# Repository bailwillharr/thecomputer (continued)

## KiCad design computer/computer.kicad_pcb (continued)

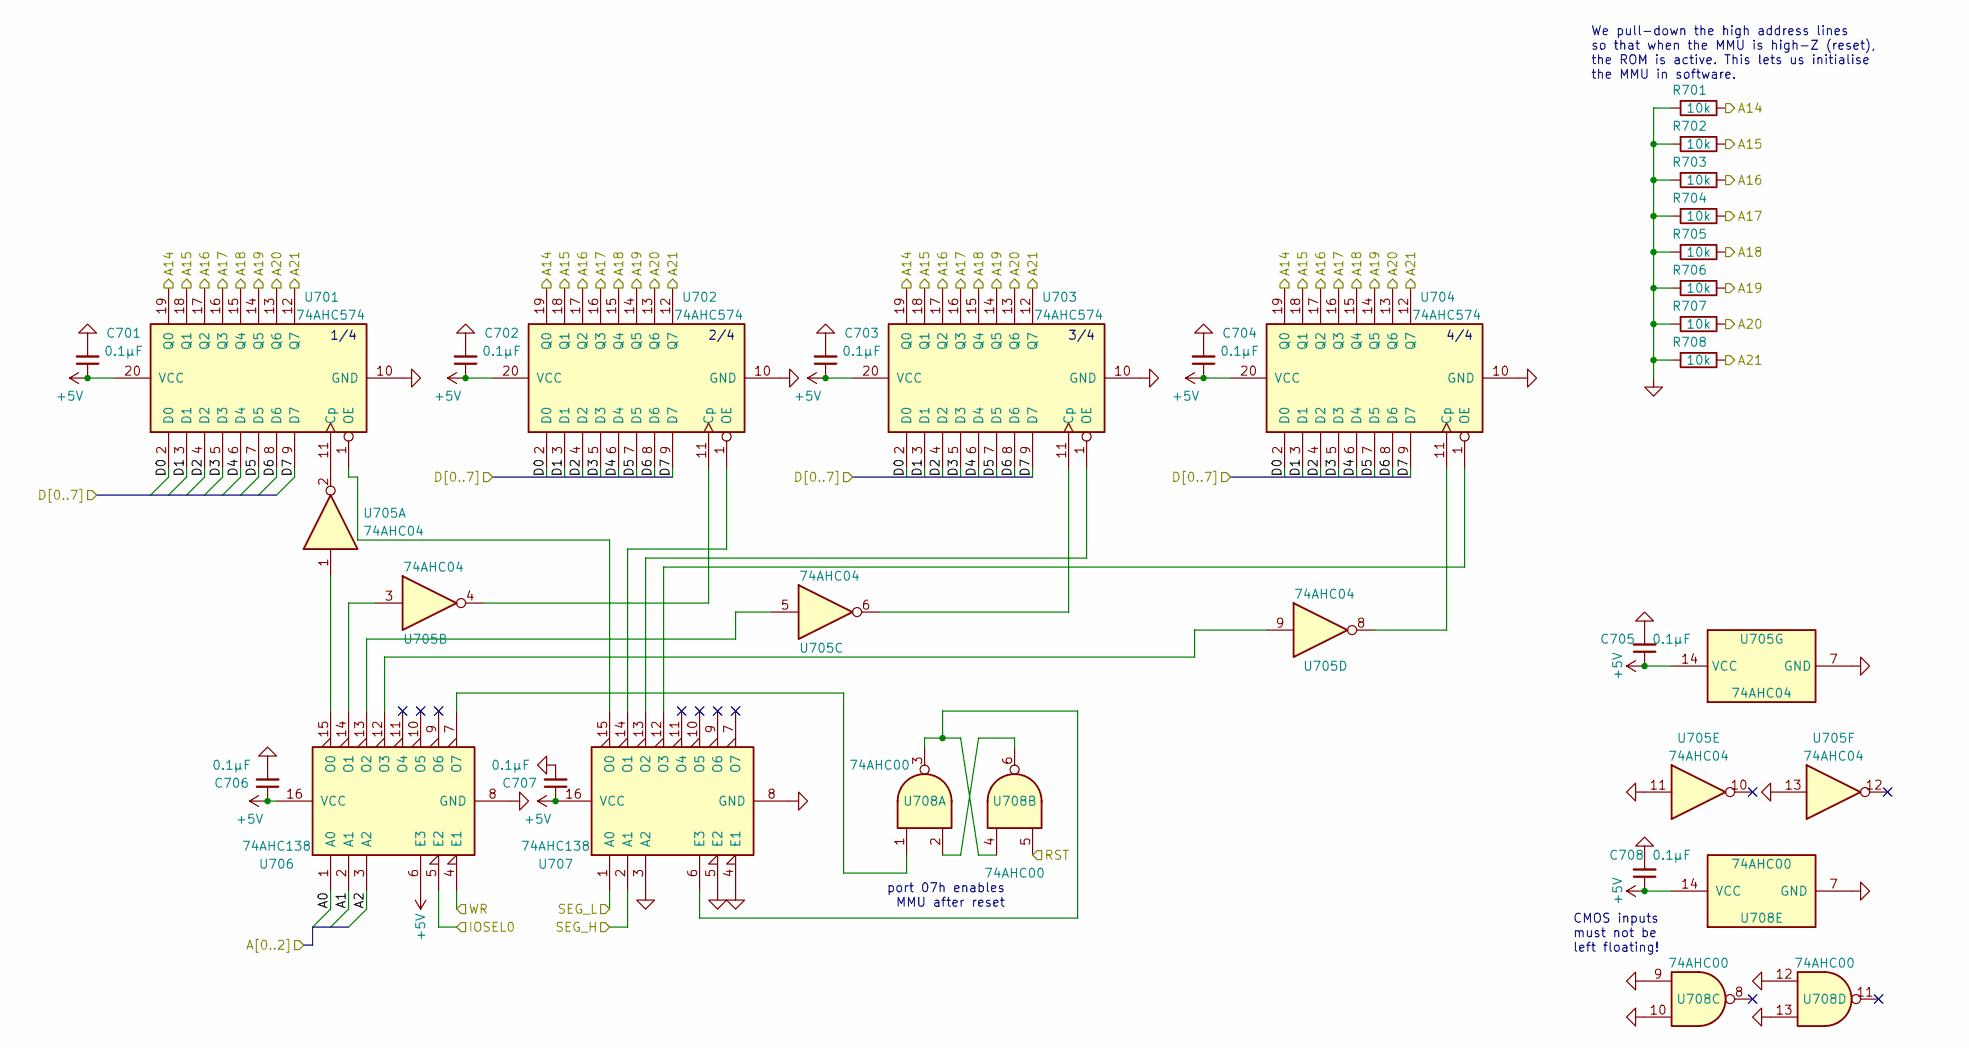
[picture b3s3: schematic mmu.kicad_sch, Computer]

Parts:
C701, C702, C703, C704, C705, C706, C707, C708: 0.1µF; C_Disc_D5.0mm_W2.5mm_P2.50mm
R701, R702, R703, R704, R705, R706, R707, R708: 10k; R_Axial_DIN0207_L6.3mm_D2.5mm_P10.16mm_Horizontal
U701, U702, U703, U704: 74AHC574; DIP-20_W7.62mm_Socket_LongPads
U705: 74AHC04; DIP-14_W7.62mm_Socket_LongPads
U706, U707: 74AHC138; DIP-16_W7.62mm_Socket_LongPads
U708: 74AHC00; DIP-14_W7.62mm_Socket_LongPads

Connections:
+5V: C701.1, C702.1, C703.1, C704.1, C705.1, C706.1, C707.1, C708.1, U701.20 (VCC), U702.20 (VCC), U703.20 (VCC), U704.20 (VCC), U705.14 (VCC), U706.6 (E3), U706.16 (VCC), U707.16 (VCC), U708.14 (VCC); also elsewhere on the board
A0: U706.1 (A0); also elsewhere on the board
A1: U706.2 (A1); also elsewhere on the board
A2: U706.3 (A2); also elsewhere on the board
A14: R701.1, U701.19 (Q0), U702.19 (Q0), U703.19 (Q0), U704.19 (Q0); also elsewhere on the board
A15: R702.1, U701.18 (Q1), U702.18 (Q1), U703.18 (Q1), U704.18 (Q1); also elsewhere on the board
A16: R703.1, U701.17 (Q2), U702.17 (Q2), U703.17 (Q2), U704.17 (Q2); also elsewhere on the board
A17: R704.1, U701.16 (Q3), U702.16 (Q3), U703.16 (Q3), U704.16 (Q3); also elsewhere on the board
A18: R705.1, U701.15 (Q4), U702.15 (Q4), U703.15 (Q4), U704.15 (Q4); also elsewhere on the board
A19: R706.1, U701.14 (Q5), U702.14 (Q5), U703.14 (Q5), U704.14 (Q5); also elsewhere on the board
A20: R707.1, U701.13 (Q6), U702.13 (Q6), U703.13 (Q6), U704.13 (Q6); also elsewhere on the board
A21: R708.1, U701.12 (Q7), U702.12 (Q7), U703.12 (Q7), U704.12 (Q7); also elsewhere on the board
CPU_A14: U707.1 (A0); also elsewhere on the board
CPU_A15: U707.2 (A1); also elsewhere on the board
D0: U701.2 (D0), U702.2 (D0), U703.2 (D0), U704.2 (D0); also elsewhere on the board
D1: U701.3 (D1), U702.3 (D1), U703.3 (D1), U704.3 (D1); also elsewhere on the board
D2: U701.4 (D2), U702.4 (D2), U703.4 (D2), U704.4 (D2); also elsewhere on the board
D3: U701.5 (D3), U702.5 (D3), U703.5 (D3), U704.5 (D3); also elsewhere on the board
D4: U701.6 (D4), U702.6 (D4), U703.6 (D4), U704.6 (D4); also elsewhere on the board
D5: U701.7 (D5), U702.7 (D5), U703.7 (D5), U704.7 (D5); also elsewhere on the board
D6: U701.8 (D6), U702.8 (D6), U703.8 (D6), U704.8 (D6); also elsewhere on the board
D7: U701.9 (D7), U702.9 (D7), U703.9 (D7), U704.9 (D7); also elsewhere on the board
GND: C701.2, C702.2, C703.2, C704.2, C705.2, C706.2, C707.2, C708.2, R701.2, R702.2, R703.2, R704.2, R705.2, R706.2, R707.2, R708.2, U701.10 (GND), U702.10 (GND), U703.10 (GND), U704.10 (GND), U705.7 (GND), U705.11, U705.13, U706.8 (GND), U707.3 (A2), U707.4 (E1), U707.5 (E2), U707.8 (GND), U708.7 (GND), U708.9, U708.10, U708.12, U708.13; also elsewhere on the board
IOSEL0: U706.5 (E2); also elsewhere on the board
unnamed: U701.1 (OE), U707.15 (O0)
unnamed: U701.11 (Cp), U705.2
unnamed: U702.1 (OE), U707.14 (O1)
unnamed: U702.11 (Cp), U705.4
unnamed: U703.1 (OE), U707.13 (O2)
unnamed: U703.11 (Cp), U705.6
unnamed: U704.1 (OE), U707.12 (O3)
unnamed: U704.11 (Cp), U705.8
unnamed: U705.1, U706.15 (O0)
unnamed: U705.3, U706.14 (O1)
unnamed: U705.5, U706.13 (O2)
unnamed: U705.9, U706.12 (O3)
unnamed: U706.7 (O7), U708.1
unnamed: U707.6 (E3), U708.3, U708.4
unnamed: U708.2, U708.6
RST: U708.5; also elsewhere on the board
WR: U706.4 (E1); also elsewhere on the board

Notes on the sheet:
1/4
4/4
2/4
We pull-down the high address lines so that when the MMU is high-Z (reset), the ROM is active. This lets us initialise the MMU in software.
port 07h enables MMU after reset
CMOS inputs must not be left floating!
3/4

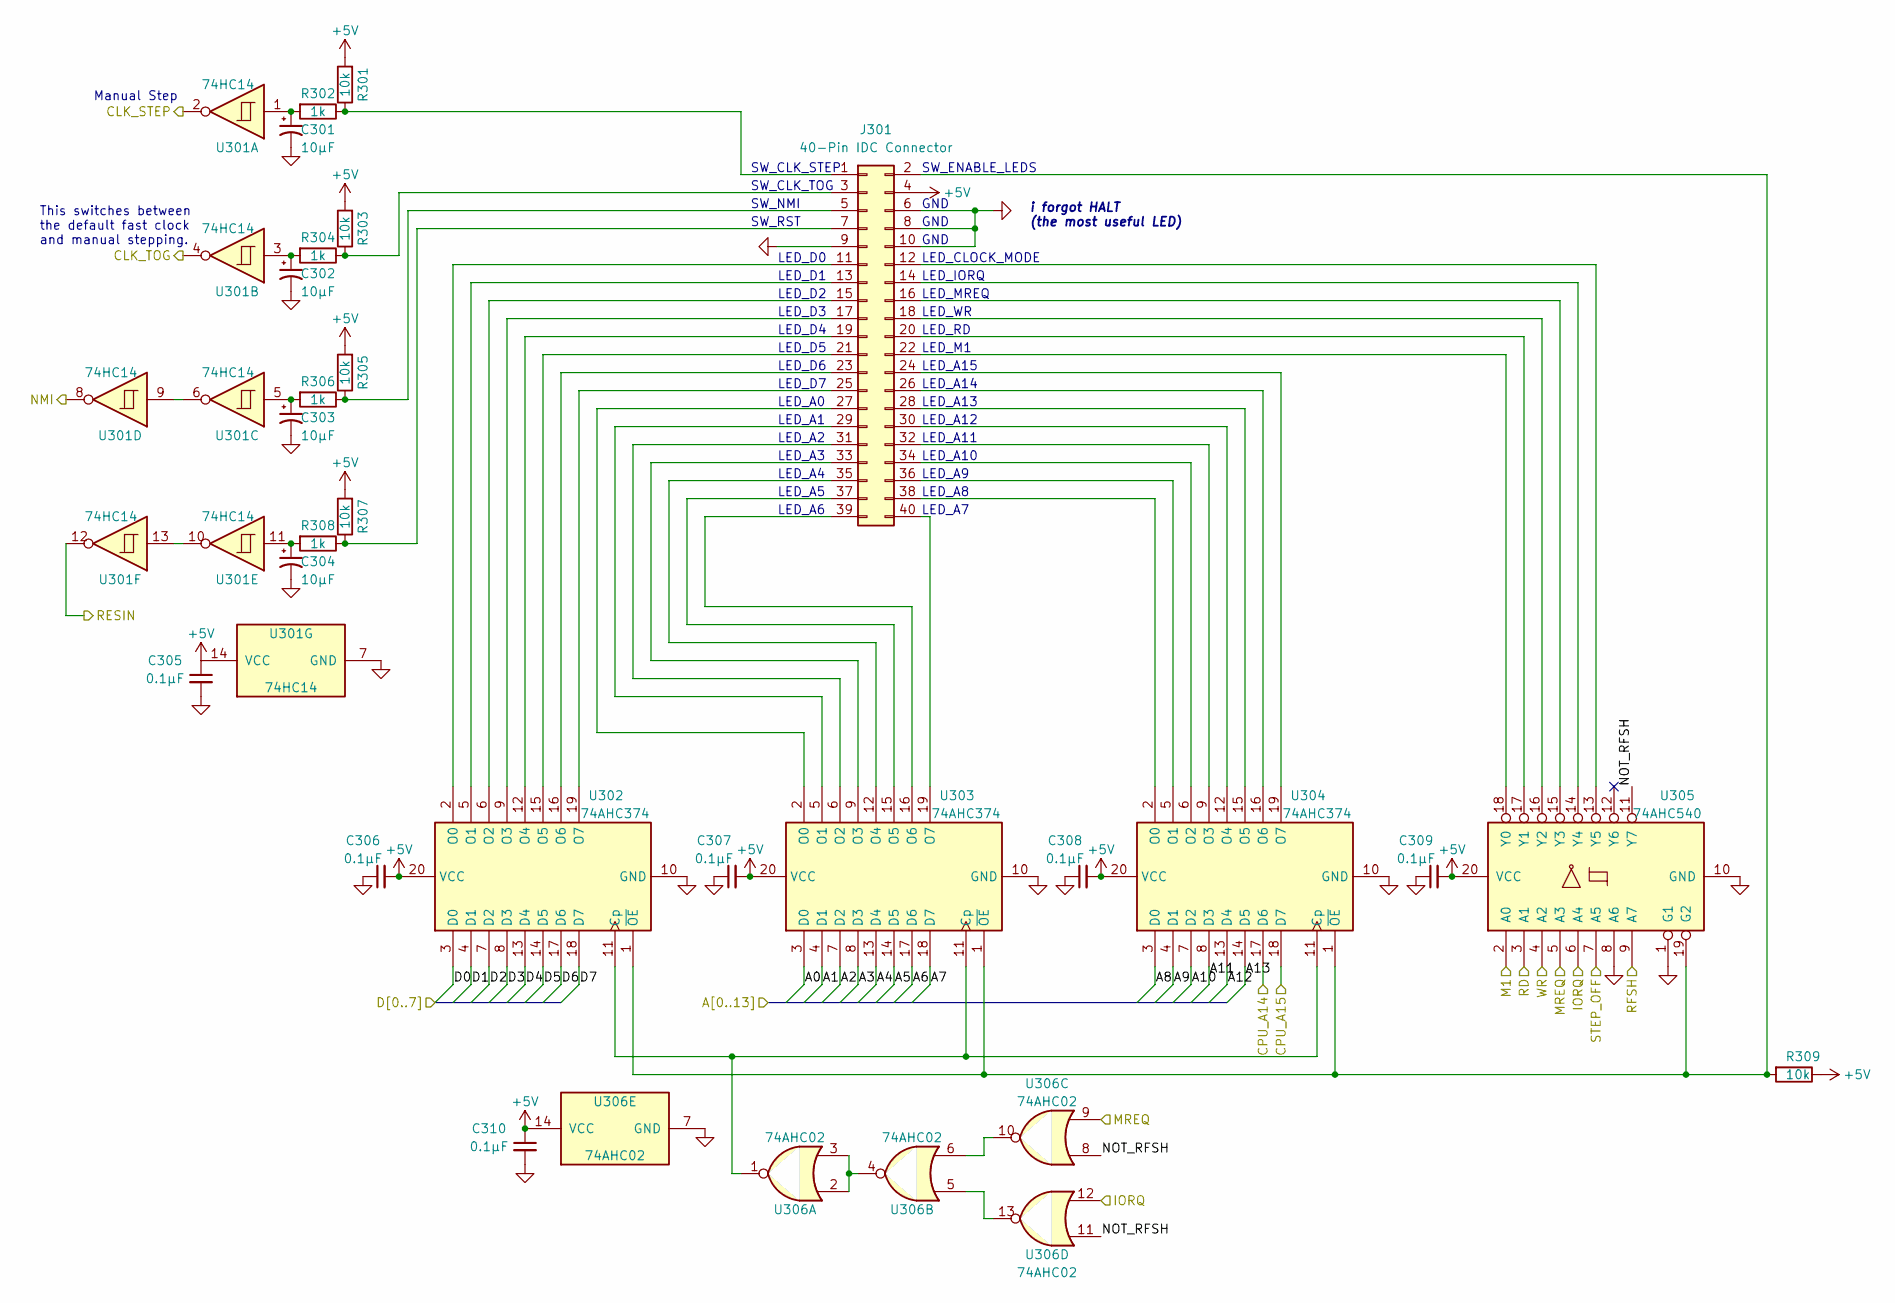
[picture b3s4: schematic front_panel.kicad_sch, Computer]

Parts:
C301, C302, C303, C304: 10µF; CP_Radial_D5.0mm_P2.50mm
C305, C306, C307, C308, C309, C310: 0.1µF; C_Disc_D5.0mm_W2.5mm_P2.50mm
J301: 40-Pin IDC Connector; IDC-Header_2x20_P2.54mm_Vertical
R301, R303, R305, R307, R309: 10k; R_Axial_DIN0207_L6.3mm_D2.5mm_P10.16mm_Horizontal
R302, R304, R306, R308: 1k; R_Axial_DIN0207_L6.3mm_D2.5mm_P10.16mm_Horizontal
U301: 74HC14; DIP-14_W7.62mm_Socket_LongPads
U302, U303, U304: 74AHC374; DIP-20_W7.62mm_Socket_LongPads
U305: 74AHC540; DIP-20_W7.62mm_Socket_LongPads
U306: 74AHC02; DIP-14_W7.62mm_Socket_LongPads

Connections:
+5V: C305.1, C306.2, C307.2, C308.2, C309.2, C310.1, J301.4, R301.2, R303.2, R305.2, R307.2, R309.1, U301.14 (VCC), U302.20 (VCC), U303.20 (VCC), U304.20 (VCC), U305.20 (VCC), U306.14 (VCC); also elsewhere on the board
/CLOCK/CLK_MAN: U301.2; also elsewhere on the board
/CLOCK/CLK_TOG: U301.4; also elsewhere on the board
/CLOCK/STEP_OFF: U305.7 (A5); also elsewhere on the board
/FRONT_PANEL/NOT_RFSH: U305.11 (Y7), U306.8, U306.11
A0: U303.3 (D0); also elsewhere on the board
A1: U303.4 (D1); also elsewhere on the board
A2: U303.7 (D2); also elsewhere on the board
A3: U303.8 (D3); also elsewhere on the board
A4: U303.13 (D4); also elsewhere on the board
A5: U303.14 (D5); also elsewhere on the board
A6: U303.17 (D6); also elsewhere on the board
A7: U303.18 (D7); also elsewhere on the board
A8: U304.3 (D0); also elsewhere on the board
A9: U304.4 (D1); also elsewhere on the board
A10: U304.7 (D2); also elsewhere on the board
A11: U304.8 (D3); also elsewhere on the board
A12: U304.13 (D4); also elsewhere on the board
A13: U304.14 (D5); also elsewhere on the board
CPU_A14: U304.17 (D6); also elsewhere on the board
CPU_A15: U304.18 (D7); also elsewhere on the board
D0: U302.3 (D0); also elsewhere on the board
D1: U302.4 (D1); also elsewhere on the board
D2: U302.7 (D2); also elsewhere on the board
D3: U302.8 (D3); also elsewhere on the board
D4: U302.13 (D4); also elsewhere on the board
D5: U302.14 (D5); also elsewhere on the board
D6: U302.17 (D6); also elsewhere on the board
D7: U302.18 (D7); also elsewhere on the board
GND: C301.2, C302.2, C303.2, C304.2, C305.2, C306.1, C307.1, C308.1, C309.1, C310.2, J301.6, J301.8, J301.9, J301.10, U301.7 (GND), U302.10 (GND), U303.10 (GND), U304.10 (GND), U305.1 (G1), U305.8 (A6), U305.10 (GND), U306.7 (GND); also elsewhere on the board
IORQ: U305.6 (A4), U306.12; also elsewhere on the board
M1: U305.2 (A0); also elsewhere on the board
MREQ: U305.5 (A3), U306.9; also elsewhere on the board
NMI: U301.8; also elsewhere on the board
unnamed: C301.1, R302.2, U301.1
unnamed: C302.1, R304.2, U301.3
unnamed: C303.1, R306.2, U301.5
unnamed: C304.1, R308.2, U301.11
unnamed: J301.1, R301.1, R302.1
unnamed: J301.2, R309.2, U302.1 (~OE), U303.1 (~OE), U304.1 (~OE), U305.19 (G2)
unnamed: J301.3, R303.1, R304.1
unnamed: J301.5, R305.1, R306.1
unnamed: J301.7, R307.1, R308.1
unnamed: J301.11, U302.2 (O0)
unnamed: J301.12, U305.13 (Y5)
unnamed: J301.13, U302.5 (O1)
unnamed: J301.14, U305.14 (Y4)
unnamed: J301.15, U302.6 (O2)
unnamed: J301.16, U305.15 (Y3)
unnamed: J301.17, U302.9 (O3)
unnamed: J301.18, U305.16 (Y2)
unnamed: J301.19, U302.12 (O4)
unnamed: J301.20, U305.17 (Y1)
unnamed: J301.21, U302.15 (O5)
unnamed: J301.22, U305.18 (Y0)
unnamed: J301.23, U302.16 (O6)
unnamed: J301.24, U304.19 (O7)
unnamed: J301.25, U302.19 (O7)
unnamed: J301.26, U304.16 (O6)
unnamed: J301.27, U303.2 (O0)
unnamed: J301.28, U304.15 (O5)
unnamed: J301.29, U303.5 (O1)
unnamed: J301.30, U304.12 (O4)
unnamed: J301.31, U303.6 (O2)
unnamed: J301.32, U304.9 (O3)
unnamed: J301.33, U303.9 (O3)
unnamed: J301.34, U304.6 (O2)
unnamed: J301.35, U303.12 (O4)
unnamed: J301.36, U304.5 (O1)
unnamed: J301.37, U303.15 (O5)
unnamed: J301.38, U304.2 (O0)
unnamed: J301.39, U303.16 (O6)
unnamed: J301.40, U303.19 (O7)
unnamed: U301.6, U301.9
unnamed: U301.10, U301.13
unnamed: U302.11 (Cp), U303.11 (Cp), U304.11 (Cp), U306.1
unnamed: U306.2, U306.3, U306.4
unnamed: U306.6, U306.10
unnamed: U306.5, U306.13
RD: U305.3 (A1); also elsewhere on the board
RESIN: U301.12; also elsewhere on the board
RFSH: U305.9 (A7); also elsewhere on the board
WR: U305.4 (A2); also elsewhere on the board

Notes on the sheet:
LED_D7
LED_A8
LED_A15
LED_A11
LED_D6
LED_A13
LED_D5
LED_A10
LED_D0
LED_D2
LED_D1
GND
LED_A0
SW_CLK_STEP
i forgot HALT (the most useful LED)
LED_A9
LED_D3
LED_A1
LED_MREQ
LED_WR
LED_M1
LED_A3
This switches between the default fast clock and manual stepping.
LED_RD
LED_A4
SW_ENABLE_LEDS
LED_IORQ
LED_CLOCK_MODE
LED_A6
SW_NMI
SW_CLK_TOG
LED_A12
LED_D4
Manual Step
LED_A2
LED_A5
SW_RST
LED_A14
LED_A7

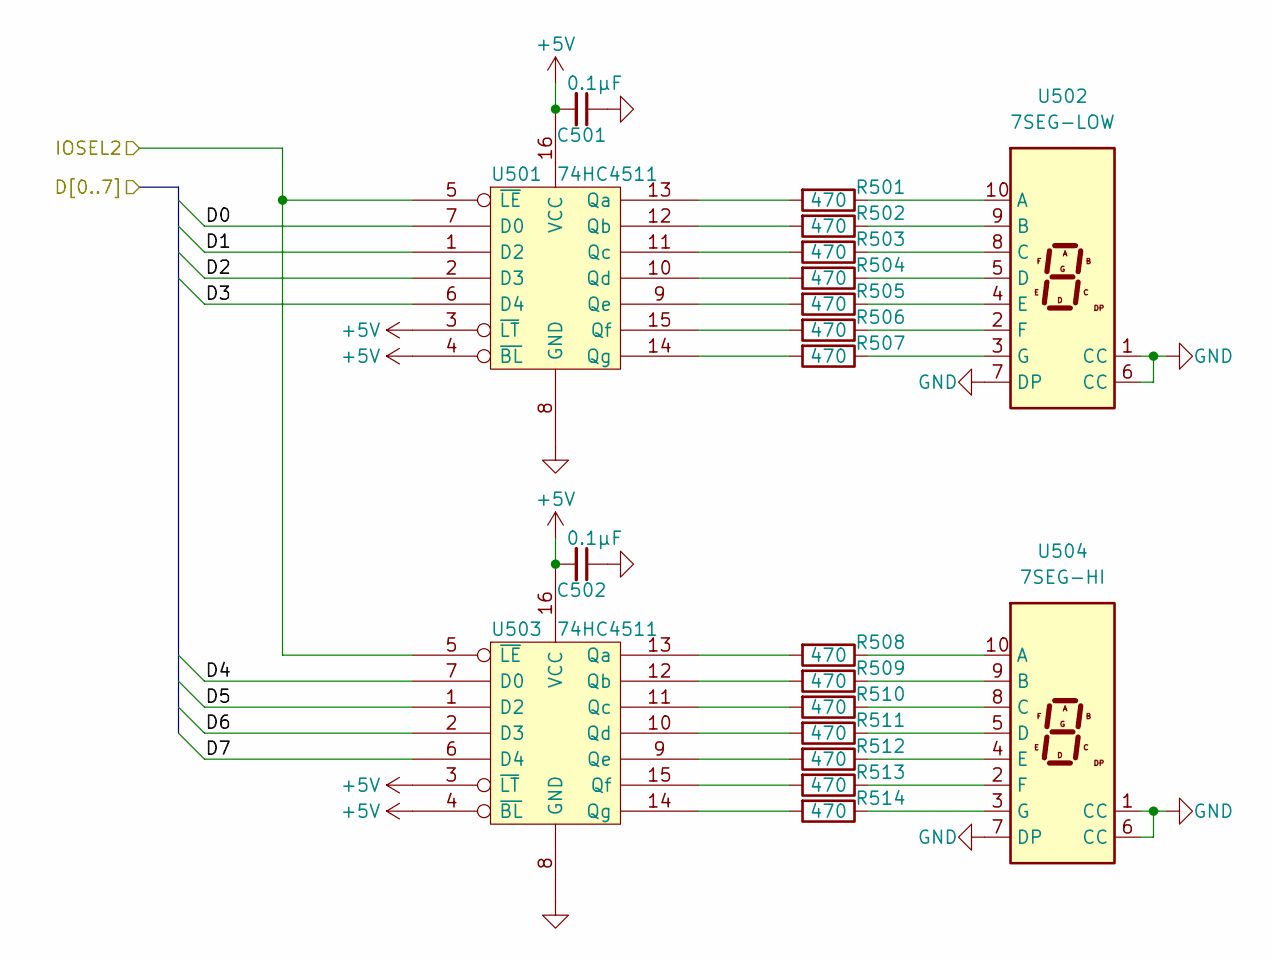
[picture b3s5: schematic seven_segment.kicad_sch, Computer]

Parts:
C501, C502: 0.1µF; C_Disc_D5.0mm_W2.5mm_P2.50mm
R501, R502, R503, R504, R505, R506, R507, R508, R509, R510, R511, R512, R513, R514: 470; R_Axial_DIN0207_L6.3mm_D2.5mm_P10.16mm_Horizontal
U501, U503: 74HC4511; DIP-16_W7.62mm_Socket_LongPads
U502: 7SEG-LOW; HDSP-A151
U504: 7SEG-HI; HDSP-A151

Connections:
+5V: C501.2, C502.2, U501.3 (~LT), U501.4 (~BL), U501.16 (VCC), U503.3 (~LT), U503.4 (~BL), U503.16 (VCC); also elsewhere on the board
D0: U501.7 (D0); also elsewhere on the board
D1: U501.1 (D2); also elsewhere on the board
D2: U501.2 (D3); also elsewhere on the board
D3: U501.6 (D4); also elsewhere on the board
D4: U503.7 (D0); also elsewhere on the board
D5: U503.1 (D2); also elsewhere on the board
D6: U503.2 (D3); also elsewhere on the board
D7: U503.6 (D4); also elsewhere on the board
GND: C501.1, C502.1, U501.8 (GND), U502.1 (CC), U502.6 (CC), U502.7 (DP), U503.8 (GND), U504.1 (CC), U504.6 (CC), U504.7 (DP); also elsewhere on the board
IOSEL2: U501.5 (~LE), U503.5 (~LE); also elsewhere on the board
unnamed: R501.1, U502.10 (A)
unnamed: R501.2, U501.13 (Qa)
unnamed: R502.1, U502.9 (B)
unnamed: R502.2, U501.12 (Qb)
unnamed: R503.1, U502.8 (C)
unnamed: R503.2, U501.11 (Qc)
unnamed: R504.1, U502.5 (D)
unnamed: R504.2, U501.10 (Qd)
unnamed: R505.1, U502.4 (E)
unnamed: R505.2, U501.9 (Qe)
unnamed: R506.1, U502.2 (F)
unnamed: R506.2, U501.15 (Qf)
unnamed: R507.1, U502.3 (G)
unnamed: R507.2, U501.14 (Qg)
unnamed: R508.1, U504.10 (A)
unnamed: R508.2, U503.13 (Qa)
unnamed: R509.1, U504.9 (B)
unnamed: R509.2, U503.12 (Qb)
unnamed: R510.1, U504.8 (C)
unnamed: R510.2, U503.11 (Qc)
unnamed: R511.1, U504.5 (D)
unnamed: R511.2, U503.10 (Qd)
unnamed: R512.1, U504.4 (E)
unnamed: R512.2, U503.9 (Qe)
unnamed: R513.1, U504.2 (F)
unnamed: R513.2, U503.15 (Qf)
unnamed: R514.1, U504.3 (G)
unnamed: R514.2, U503.14 (Qg)

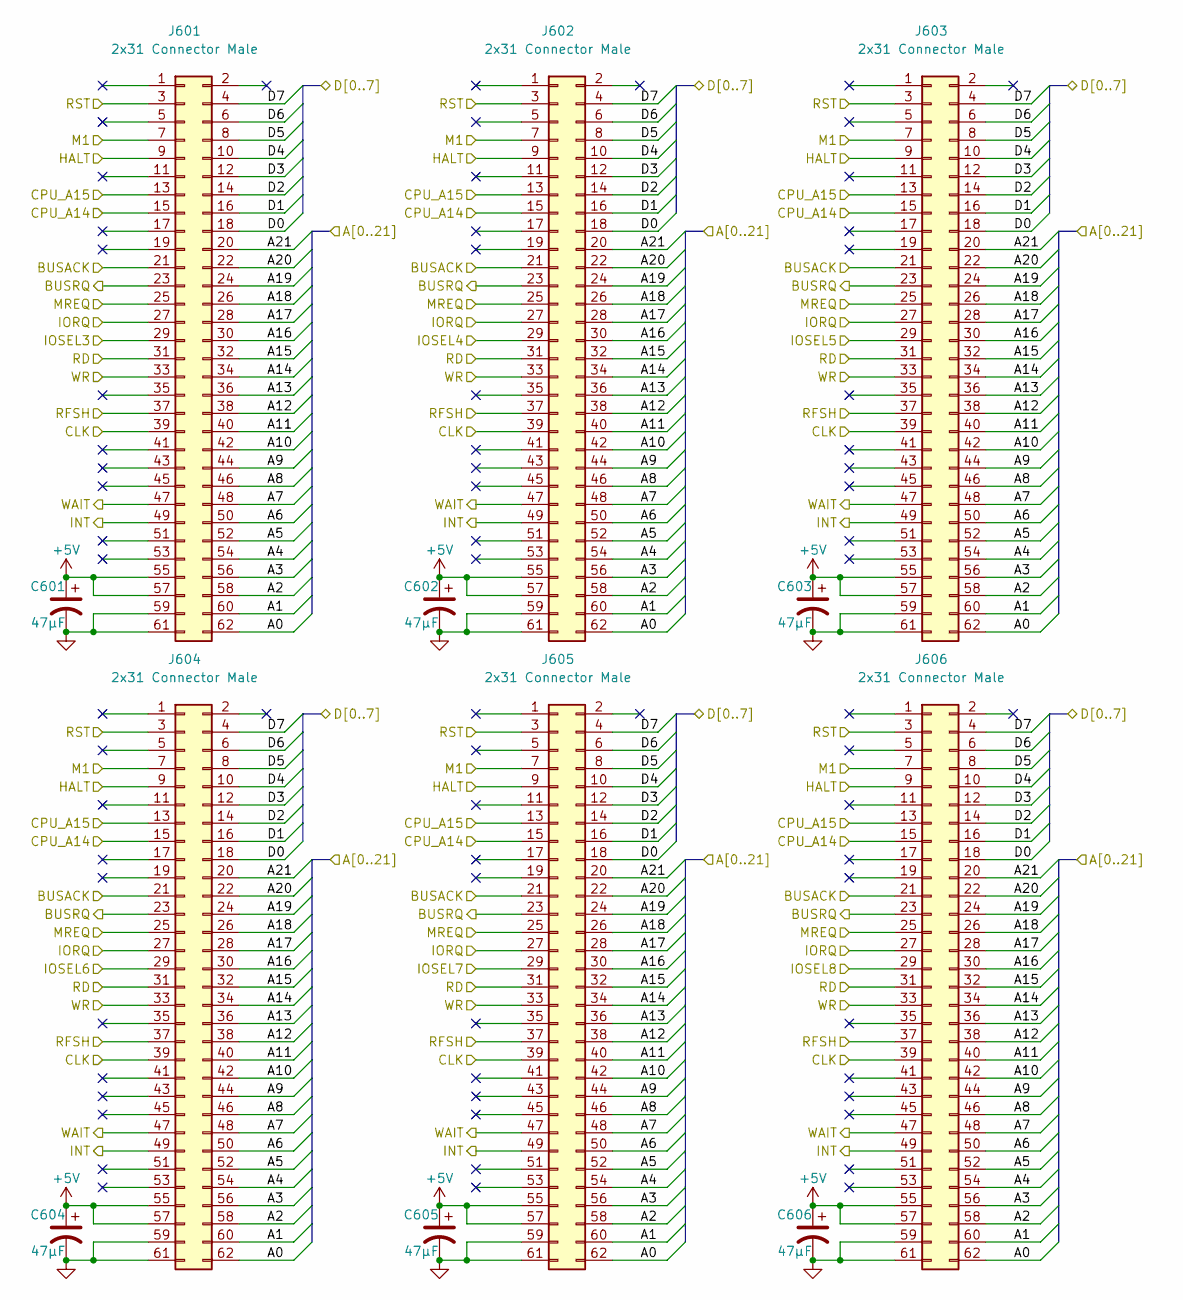
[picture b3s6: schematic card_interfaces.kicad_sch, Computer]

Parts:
C601, C602, C603, C604, C605, C606: 47µF; CP_Radial_D5.0mm_P2.50mm
J601, J602, J603, J604, J605, J606: 2x31 Connector Male; PinHeader_2x31_P2.54mm_Vertical

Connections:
+5V: C601.1, C602.1, C603.1, C604.1, C605.1, C606.1, J601.55, J601.57, J602.55, J602.57, J603.55, J603.57, J604.55, J604.57, J605.55, J605.57, J606.55, J606.57; also elsewhere on the board
A0: J601.62, J602.62, J603.62, J604.62, J605.62, J606.62; also elsewhere on the board
A1: J601.60, J602.60, J603.60, J604.60, J605.60, J606.60; also elsewhere on the board
A2: J601.58, J602.58, J603.58, J604.58, J605.58, J606.58; also elsewhere on the board
A3: J601.56, J602.56, J603.56, J604.56, J605.56, J606.56; also elsewhere on the board
A4: J601.54, J602.54, J603.54, J604.54, J605.54, J606.54; also elsewhere on the board
A5: J601.52, J602.52, J603.52, J604.52, J605.52, J606.52; also elsewhere on the board
A6: J601.50, J602.50, J603.50, J604.50, J605.50, J606.50; also elsewhere on the board
A7: J601.48, J602.48, J603.48, J604.48, J605.48, J606.48; also elsewhere on the board
A8: J601.46, J602.46, J603.46, J604.46, J605.46, J606.46; also elsewhere on the board
A9: J601.44, J602.44, J603.44, J604.44, J605.44, J606.44; also elsewhere on the board
A10: J601.42, J602.42, J603.42, J604.42, J605.42, J606.42; also elsewhere on the board
A11: J601.40, J602.40, J603.40, J604.40, J605.40, J606.40; also elsewhere on the board
A12: J601.38, J602.38, J603.38, J604.38, J605.38, J606.38; also elsewhere on the board
A13: J601.36, J602.36, J603.36, J604.36, J605.36, J606.36; also elsewhere on the board
A14: J601.34, J602.34, J603.34, J604.34, J605.34, J606.34; also elsewhere on the board
A15: J601.32, J602.32, J603.32, J604.32, J605.32, J606.32; also elsewhere on the board
A16: J601.30, J602.30, J603.30, J604.30, J605.30, J606.30; also elsewhere on the board
A17: J601.28, J602.28, J603.28, J604.28, J605.28, J606.28; also elsewhere on the board
A18: J601.26, J602.26, J603.26, J604.26, J605.26, J606.26; also elsewhere on the board
A19: J601.24, J602.24, J603.24, J604.24, J605.24, J606.24; also elsewhere on the board
A20: J601.22, J602.22, J603.22, J604.22, J605.22, J606.22; also elsewhere on the board
A21: J601.20, J602.20, J603.20, J604.20, J605.20, J606.20; also elsewhere on the board
BUSACK: J601.21, J602.21, J603.21, J604.21, J605.21, J606.21; also elsewhere on the board
BUSRQ: J601.23, J602.23, J603.23, J604.23, J605.23, J606.23; also elsewhere on the board
CLK: J601.39, J602.39, J603.39, J604.39, J605.39, J606.39; also elsewhere on the board
CPU_A14: J601.15, J602.15, J603.15, J604.15, J605.15, J606.15; also elsewhere on the board
CPU_A15: J601.13, J602.13, J603.13, J604.13, J605.13, J606.13; also elsewhere on the board
D0: J601.18, J602.18, J603.18, J604.18, J605.18, J606.18; also elsewhere on the board
D1: J601.16, J602.16, J603.16, J604.16, J605.16, J606.16; also elsewhere on the board
D2: J601.14, J602.14, J603.14, J604.14, J605.14, J606.14; also elsewhere on the board
D3: J601.12, J602.12, J603.12, J604.12, J605.12, J606.12; also elsewhere on the board
D4: J601.10, J602.10, J603.10, J604.10, J605.10, J606.10; also elsewhere on the board
D5: J601.8, J602.8, J603.8, J604.8, J605.8, J606.8; also elsewhere on the board
D6: J601.6, J602.6, J603.6, J604.6, J605.6, J606.6; also elsewhere on the board
D7: J601.4, J602.4, J603.4, J604.4, J605.4, J606.4; also elsewhere on the board
GND: C601.2, C602.2, C603.2, C604.2, C605.2, C606.2, J601.59, J601.61, J602.59, J602.61, J603.59, J603.61, J604.59, J604.61, J605.59, J605.61, J606.59, J606.61; also elsewhere on the board
HALT: J601.9, J602.9, J603.9, J604.9, J605.9, J606.9; also elsewhere on the board
INT: J601.49, J602.49, J603.49, J604.49, J605.49, J606.49; also elsewhere on the board
IORQ: J601.27, J602.27, J603.27, J604.27, J605.27, J606.27; also elsewhere on the board
IOSEL3: J601.29; also elsewhere on the board
IOSEL4: J602.29; also elsewhere on the board
IOSEL5: J603.29; also elsewhere on the board
IOSEL6: J604.29; also elsewhere on the board
IOSEL7: J605.29; also elsewhere on the board
IOSEL8: J606.29; also elsewhere on the board
M1: J601.7, J602.7, J603.7, J604.7, J605.7, J606.7; also elsewhere on the board
MREQ: J601.25, J602.25, J603.25, J604.25, J605.25, J606.25; also elsewhere on the board
RD: J601.31, J602.31, J603.31, J604.31, J605.31, J606.31; also elsewhere on the board
RFSH: J601.37, J602.37, J603.37, J604.37, J605.37, J606.37; also elsewhere on the board
RST: J601.3, J602.3, J603.3, J604.3, J605.3, J606.3; also elsewhere on the board
WAIT: J601.47, J602.47, J603.47, J604.47, J605.47, J606.47; also elsewhere on the board
WR: J601.33, J602.33, J603.33, J604.33, J605.33, J606.33; also elsewhere on the board

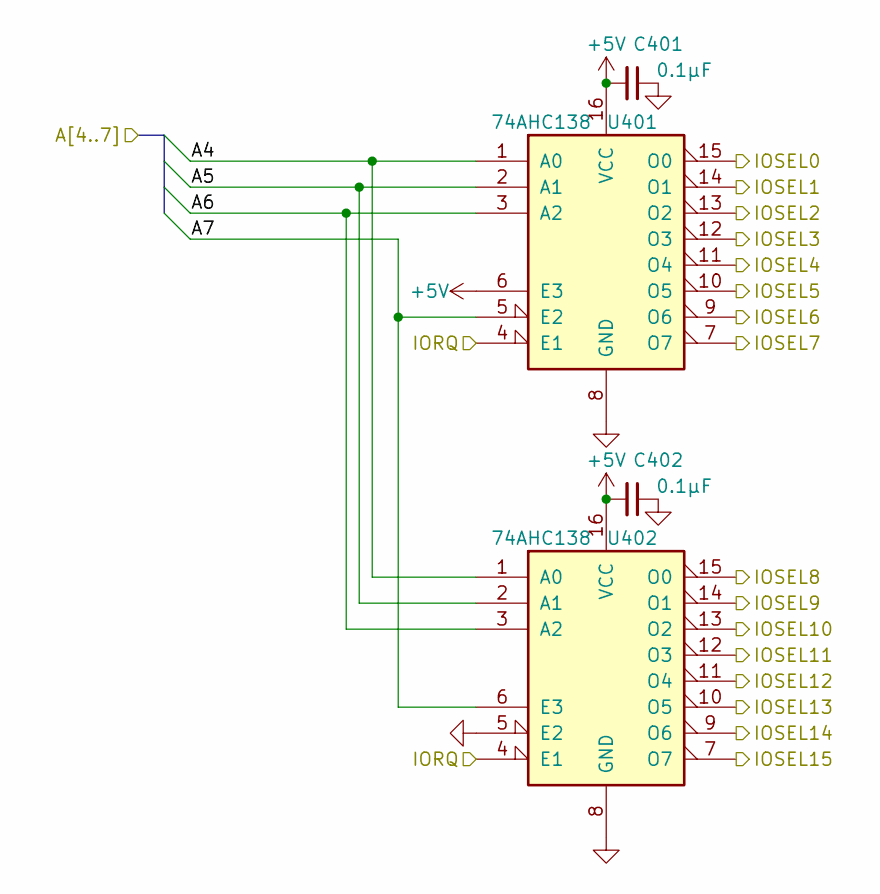
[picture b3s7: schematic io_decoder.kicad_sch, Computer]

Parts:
C401, C402: 0.1µF; C_Disc_D5.0mm_W2.5mm_P2.50mm
U401, U402: 74AHC138; DIP-16_W7.62mm_Socket_LongPads

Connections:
+5V: C401.2, C402.2, U401.6 (E3), U401.16 (VCC), U402.16 (VCC); also elsewhere on the board
A4: U401.1 (A0), U402.1 (A0); also elsewhere on the board
A5: U401.2 (A1), U402.2 (A1); also elsewhere on the board
A6: U401.3 (A2), U402.3 (A2); also elsewhere on the board
A7: U401.5 (E2), U402.6 (E3); also elsewhere on the board
GND: C401.1, C402.1, U401.8 (GND), U402.5 (E2), U402.8 (GND); also elsewhere on the board
IORQ: U401.4 (E1), U402.4 (E1); also elsewhere on the board
IOSEL0: U401.15 (O0); also elsewhere on the board
IOSEL1: U401.14 (O1); also elsewhere on the board
IOSEL2: U401.13 (O2); also elsewhere on the board
IOSEL3: U401.12 (O3); also elsewhere on the board
IOSEL4: U401.11 (O4); also elsewhere on the board
IOSEL5: U401.10 (O5); also elsewhere on the board
IOSEL6: U401.9 (O6); also elsewhere on the board
IOSEL7: U401.7 (O7); also elsewhere on the board
IOSEL8: U402.15 (O0); also elsewhere on the board

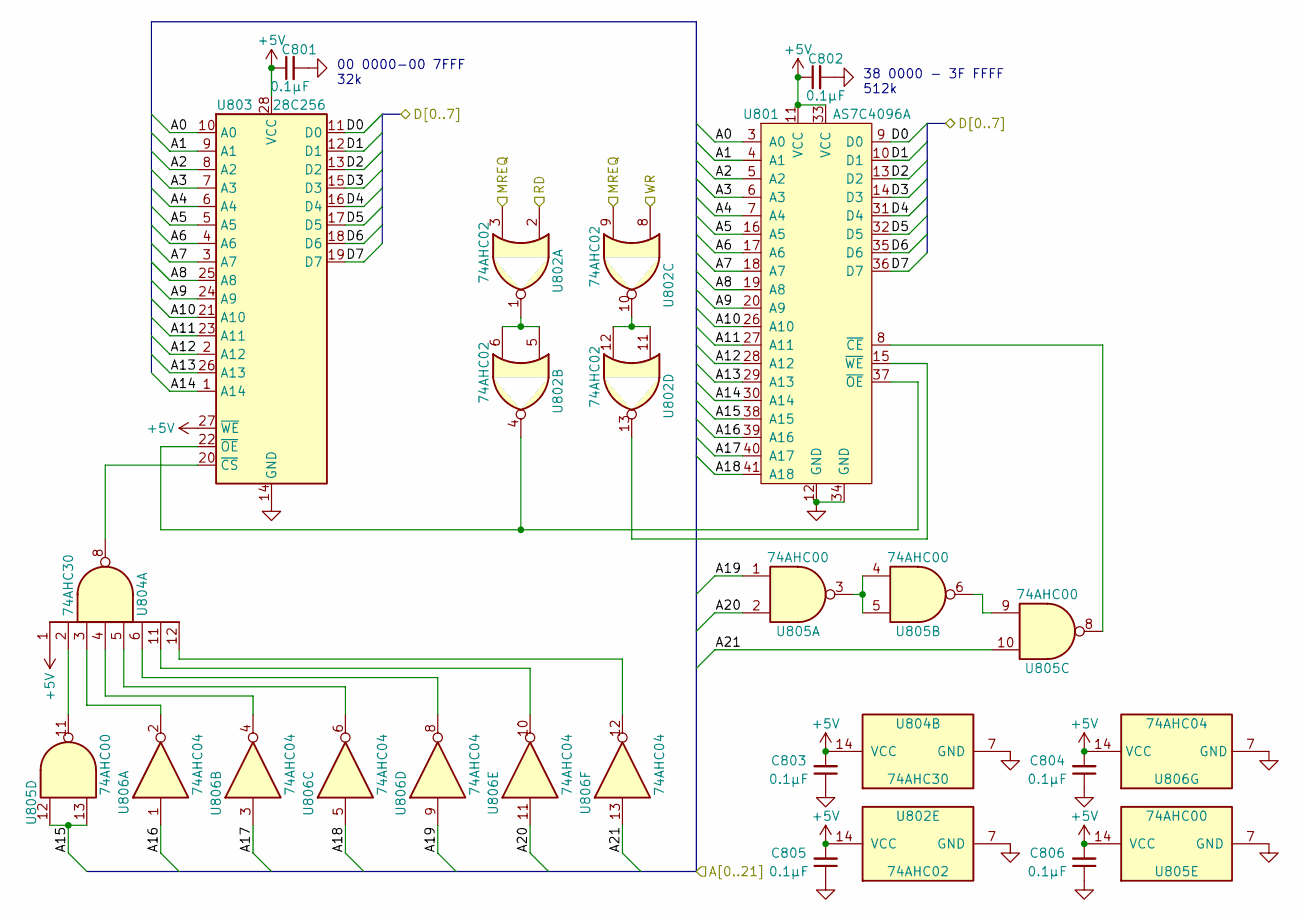
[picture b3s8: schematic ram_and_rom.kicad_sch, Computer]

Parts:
C801, C802, C803, C804, C805, C806: 0.1µF; C_Disc_D5.0mm_W2.5mm_P2.50mm
U801: AS7C4096A; TSOP-II-44_10.16x18.41mm_P0.8mm
U802: 74AHC02; DIP-14_W7.62mm_Socket_LongPads
U803: 28C256; DIP-28_W15.24mm_Socket_LongPads
U804: 74AHC30; DIP-14_W7.62mm_Socket_LongPads
U805: 74AHC00; DIP-14_W7.62mm_Socket_LongPads
U806: 74AHC04; DIP-14_W7.62mm_Socket_LongPads

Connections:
+5V: C801.1, C802.1, C803.2, C804.2, C805.2, C806.2, U801.11 (VCC), U801.33 (VCC), U802.14 (VCC), U803.27 (~WE), U803.28 (VCC), U804.1, U804.14 (VCC), U805.14 (VCC), U806.14 (VCC); also elsewhere on the board
A0: U801.3 (A0), U803.10 (A0); also elsewhere on the board
A1: U801.4 (A1), U803.9 (A1); also elsewhere on the board
A2: U801.5 (A2), U803.8 (A2); also elsewhere on the board
A3: U801.6 (A3), U803.7 (A3); also elsewhere on the board
A4: U801.7 (A4), U803.6 (A4); also elsewhere on the board
A5: U801.16 (A5), U803.5 (A5); also elsewhere on the board
A6: U801.17 (A6), U803.4 (A6); also elsewhere on the board
A7: U801.18 (A7), U803.3 (A7); also elsewhere on the board
A8: U801.19 (A8), U803.25 (A8); also elsewhere on the board
A9: U801.20 (A9), U803.24 (A9); also elsewhere on the board
A10: U801.26 (A10), U803.21 (A10); also elsewhere on the board
A11: U801.27 (A11), U803.23 (A11); also elsewhere on the board
A12: U801.28 (A12), U803.2 (A12); also elsewhere on the board
A13: U801.29 (A13), U803.26 (A13); also elsewhere on the board
A14: U801.30 (A14), U803.1 (A14); also elsewhere on the board
A15: U801.38 (A15), U805.12, U805.13; also elsewhere on the board
A16: U801.39 (A16), U806.1; also elsewhere on the board
A17: U801.40 (A17), U806.3; also elsewhere on the board
A18: U801.41 (A18), U806.5; also elsewhere on the board
A19: U805.1, U806.9; also elsewhere on the board
A20: U805.2, U806.11; also elsewhere on the board
A21: U805.10, U806.13; also elsewhere on the board
D0: U801.9 (D0), U803.11 (D0); also elsewhere on the board
D1: U801.10 (D1), U803.12 (D1); also elsewhere on the board
D2: U801.13 (D2), U803.13 (D2); also elsewhere on the board
D3: U801.14 (D3), U803.15 (D3); also elsewhere on the board
D4: U801.31 (D4), U803.16 (D4); also elsewhere on the board
D5: U801.32 (D5), U803.17 (D5); also elsewhere on the board
D6: U801.35 (D6), U803.18 (D6); also elsewhere on the board
D7: U801.36 (D7), U803.19 (D7); also elsewhere on the board
GND: C801.2, C802.2, C803.1, C804.1, C805.1, C806.1, U801.12 (GND), U801.34 (GND), U802.7 (GND), U803.14 (GND), U804.7 (GND), U805.7 (GND), U806.7 (GND); also elsewhere on the board
MREQ: U802.3, U802.9; also elsewhere on the board
unnamed: U801.8 (~CE), U805.8
unnamed: U801.15 (~WE), U802.13
unnamed: U801.37 (~OE), U802.4, U803.22 (~OE)
unnamed: U802.1, U802.5, U802.6
unnamed: U802.10, U802.11, U802.12
unnamed: U803.20 (~CS), U804.8
unnamed: U804.2, U805.11
unnamed: U804.3, U806.2
unnamed: U804.4, U806.4
unnamed: U804.5, U806.6
unnamed: U804.6, U806.8
unnamed: U804.11, U806.10
unnamed: U804.12, U806.12
unnamed: U805.3, U805.4, U805.5
unnamed: U805.6, U805.9
RD: U802.2; also elsewhere on the board
WR: U802.8; also elsewhere on the board

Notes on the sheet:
38 0000 - 3F FFFF 512k
00 0000-00 7FFF 32k

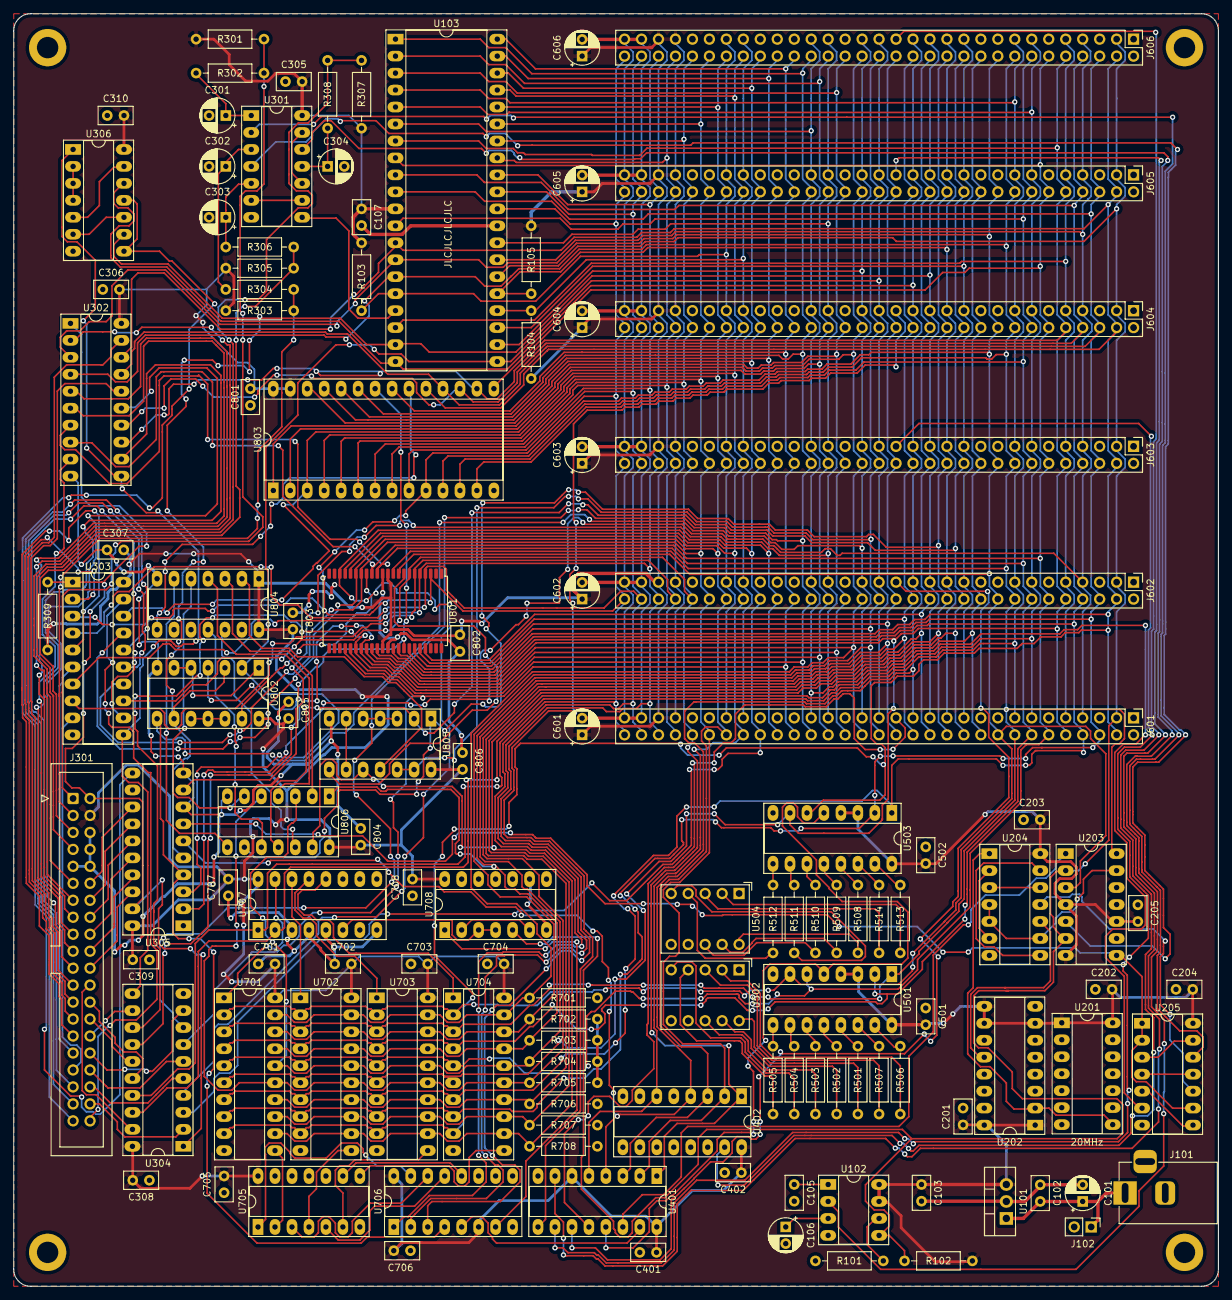
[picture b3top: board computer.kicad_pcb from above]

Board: 2 copper layers, 180.3 x 190.5 mm, 124 parts (0 on the bottom side), 179 nets.

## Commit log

2023-03-07 add shared libraries
2023-03-07 Remove unneeded files
2023-03-08 Tidy up
2023-03-09 remove backups
2023-06-03 Do things
